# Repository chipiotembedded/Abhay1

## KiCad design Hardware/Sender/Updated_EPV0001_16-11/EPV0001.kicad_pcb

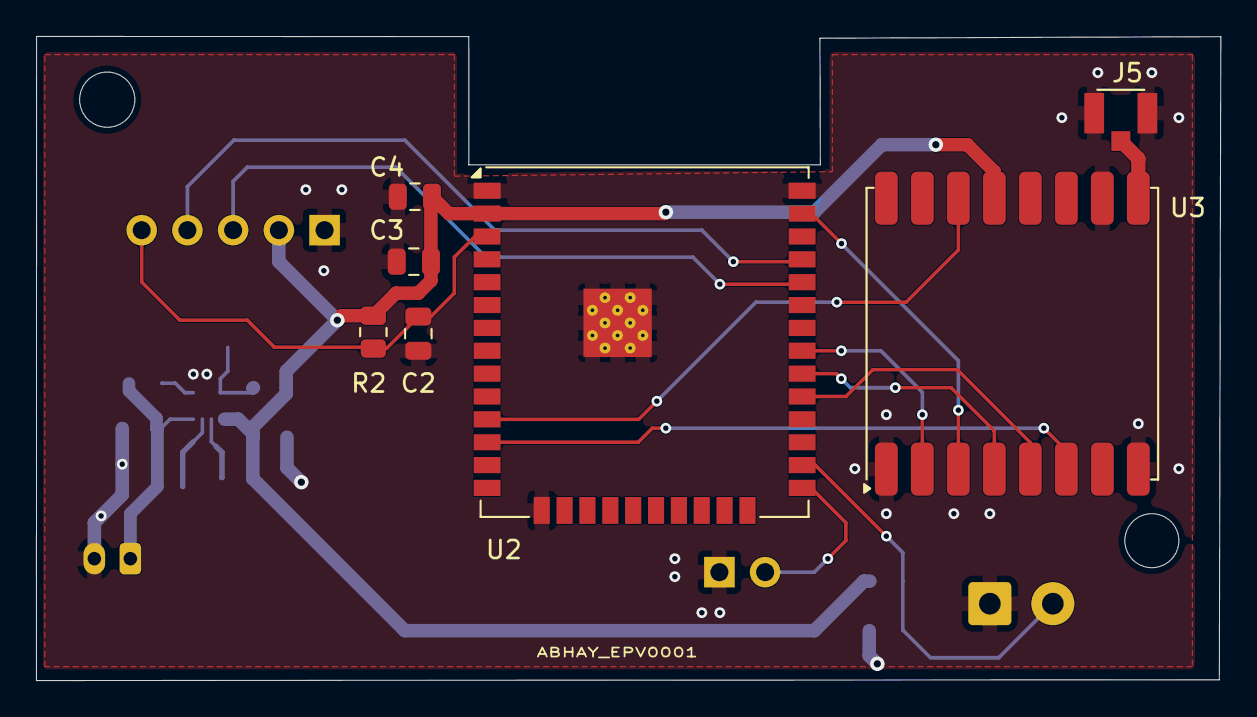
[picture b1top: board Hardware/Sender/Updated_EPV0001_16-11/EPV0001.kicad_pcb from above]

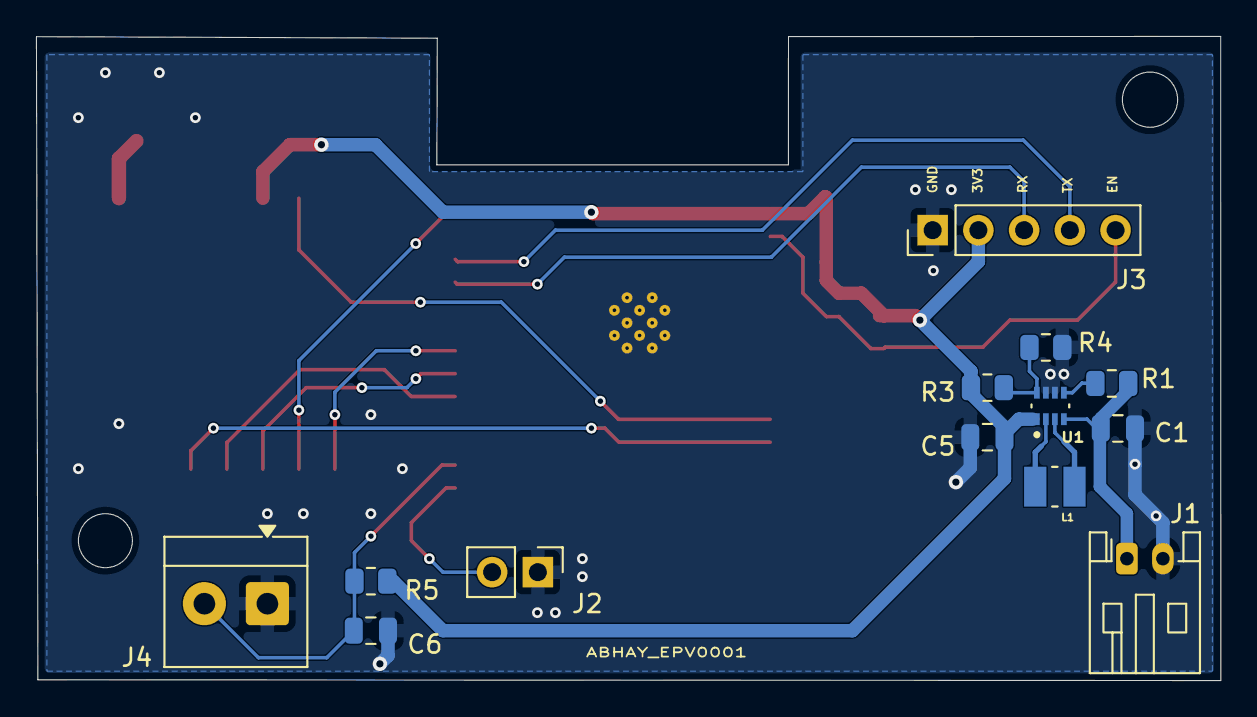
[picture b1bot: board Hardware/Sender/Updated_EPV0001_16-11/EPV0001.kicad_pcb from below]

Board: 2 copper layers, 65.8 x 35.8 mm, 20 parts (13 on the bottom side), 19 nets.

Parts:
C1, C3: 22uf; C_0805_2012Metric
C2, C4, C6: 0.1uf; C_0805_2012Metric
C5: 47 uF; C_0805_2012Metric
J1: batt IN; JST_PH_S2B-PH-K_1x02_P2.00mm_Horizontal
J2: Boot Button; PinHeader_1x02_P2.54mm_Vertical
J3: Code_Flasher; PinHeader_1x05_P2.54mm_Vertical
J4: Main switch; TerminalBlock_4Ucon_1x02_P3.50mm_Horizontal
J5: U.FL-R-SMT_01_; HRS_U.FL-R-SMT_01_
L1: DFE252012P-1R0M=P2; INDC2520X120N
R1: 100k ohm; R_0805_2012Metric
R2, R5: 10k; R_0805_2012Metric
R3: 511k ohm; R_0805_2012Metric
R4: 91k ohm; R_0805_2012Metric
U1: TPS631000DRLR; SOT50P160X60-8N
U2: ESP32-WROOM-32UE
U3: RFM95W-868S2; HOPERF_RFM9XW_SMD

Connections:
+3.3V: C3.1, C4.1, C5.1, J3.2, R2.1, R3.1, R5.1, U1.1 (VOUT), U2.2 (VDD), U3.13 (3.3V)
GND: C1.2, C2.1, C3.2, C4.2, C5.2, C6.1, J1.2, J2.1, J3.1, J4.1, J5.1 (GND), J5.2 (GND), R4.2, U1.6 (MODE), U1.7 (GND), U2.1 (GND), U2.15 (GND), U2.38 (GND), U2.39 (GND), U3.1 (GND), U3.8 (GND), U3.10 (GND)
unnamed: C1.1, J1.1, R1.1, U1.4 (VIN)
unnamed: J2.2, U2.25 (IO0)
unnamed: J3.3, U2.34 (RXD0/IO3)
unnamed: J3.4, U2.35 (TXD0/IO1)
unnamed: C2.2, J3.5, R2.2, U2.3 (EN)
unnamed: C6.2, J4.2, R5.2, U2.26 (IO4)
unnamed: J5.3 (SIG), U3.9 (ANT)
unnamed: R1.2, U1.5 (EN)
unnamed: R3.2, R4.1, U1.8 (FB)
unnamed: L1.1, U1.3 (LX1)
unnamed: L1.2, U1.2 (LX2)
unnamed: U2.29 (IO5), U3.5 (NSS)
unnamed: U2.30 (IO18), U3.4 (SCK)
unnamed: U2.31 (IO19), U3.2 (MISO)
unnamed: U2.37 (IO23), U3.3 (MOSI)
unnamed: U2.11 (IO26), U3.14 (DIO0)
unnamed: U2.12 (IO27), U3.6 (RESET)

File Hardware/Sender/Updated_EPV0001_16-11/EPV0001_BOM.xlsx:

Reference | Value | Footprint/ Discription | Datasheet | Qty | MANUFACTURER
C1,C3 | 22uf | Capacitor_SMD:C_0805_2012Metric | GRM187R61A226ME15, 22 µF, 6.3 V | 2 | Murata
C2,C4,C6 | 0.1uf | Capacitor_SMD:C_0805_2012Metric |  | 3
C5 | 47 uF | Capacitor_SMD:C_0805_2012Metric | GRM219R60J476ME44, 47 µF, 6.3 V | 1 | Murata
J1 | batt IN | Connector_JST:JST_PH_S2B-PH-K_1x02_P2.00mm_Horizontal |  | 1
J2 | Boot Button | Connector_PinHeader_2.54mm:PinHeader_1x02_P2.54mm_Vertical |  | 1
J3 | Code_Flasher | Connector_PinHeader_2.54mm:PinHeader_1x05_P2.54mm_Vertical |  | 1
J4 | Main switch | TerminalBlock_4Ucon:TerminalBlock_4Ucon_1x02_P3.50mm_Horizontal |  | 1
J5 | U.FL-R-SMT_01_ | LORA Antenna:HRS_U.FL-R-SMT_01_ |  | 1
L1 | 1 uH | Inductor_SMD:L_APV_ANR252012 | DFE252012P-1R0M=P2 | 1 | Murata
R1 | 100k ohm | Resistor_SMD:R_0805_2012Metric |  | 1
R2,R5 | 10k | Resistor_SMD:R_0805_2012Metric |  | 2
R3 | 511k ohm | Resistor_SMD:R_0805_2012Metric |  | 1
R4 | 91k ohm | Resistor_SMD:R_0805_2012Metric |  | 1
U1 | TPS631000DRLR | TPS631000DRLR:SOT50P160X60-8N | https://www.ti.com/product/TPS631000/part-details/TPS631000DRLR | 1 | Texas Instruments
U2 | ESP32-WROOM-32UE | RF_Module:ESP32-WROOM-32UE | https://www.espressif.com/sites/default/files/documentation/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 | 1
U3 | RFM95W-868S2 | RF_Module:HOPERF_RFM9XW_SMD | https://www.hoperf.com/data/upload/portal/20181127/5bfcbea20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 | 1
 | TP4056 | TP4056 1A Li Ion Lithium Battery Charging Module With Current Protection Type C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 | https://robu.in/product/tp4056-1a-li-ion-lithium-battery-cha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 | 1
 | TP4056 Panel Mount 3D Printed Housing | TP4056 USB-C Panel Mount 3D Printed Housing enclosure that securely houses the 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 | https://www.amazon.in/Printed-Snap-Fit-Enclosure-Electronics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 | 1
 | Lipo battery | 3.7V 2000mAh Li-Po Rechargeable Battery (Lithium Polymer Battery Pack) | https://rajivelectronics.com/product/3-7v-2000mah-li-po-rech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 | 1
 | Interface cable | SMA FEMALE TO UFL ANTENNA EXT -200MM | https://rajivelectronics.com/product/sma-female-to-ufl-anten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 | 1
 | ANTENNA | 2.4 GHZ/3 DB AT 5 GHZ SMA MALE RUBBER DUCK WIFI FOLDING ANTENNA-105 MM | https://rajivelectronics.com/product/2-4ghz-5ghz-sma-male-ru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
 | JST - Connector with wire | JST-PH-2 -2 Pin Double Sided Female To Female Connector With 2mm Pitch -30cm Wi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 | https://sharvielectronics.com/product/jst-ph-2-2-pin-double-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 | 1
 | Main button | Door Exit Metel push buttorn |  | 1
 | Enclosure metel box with screw

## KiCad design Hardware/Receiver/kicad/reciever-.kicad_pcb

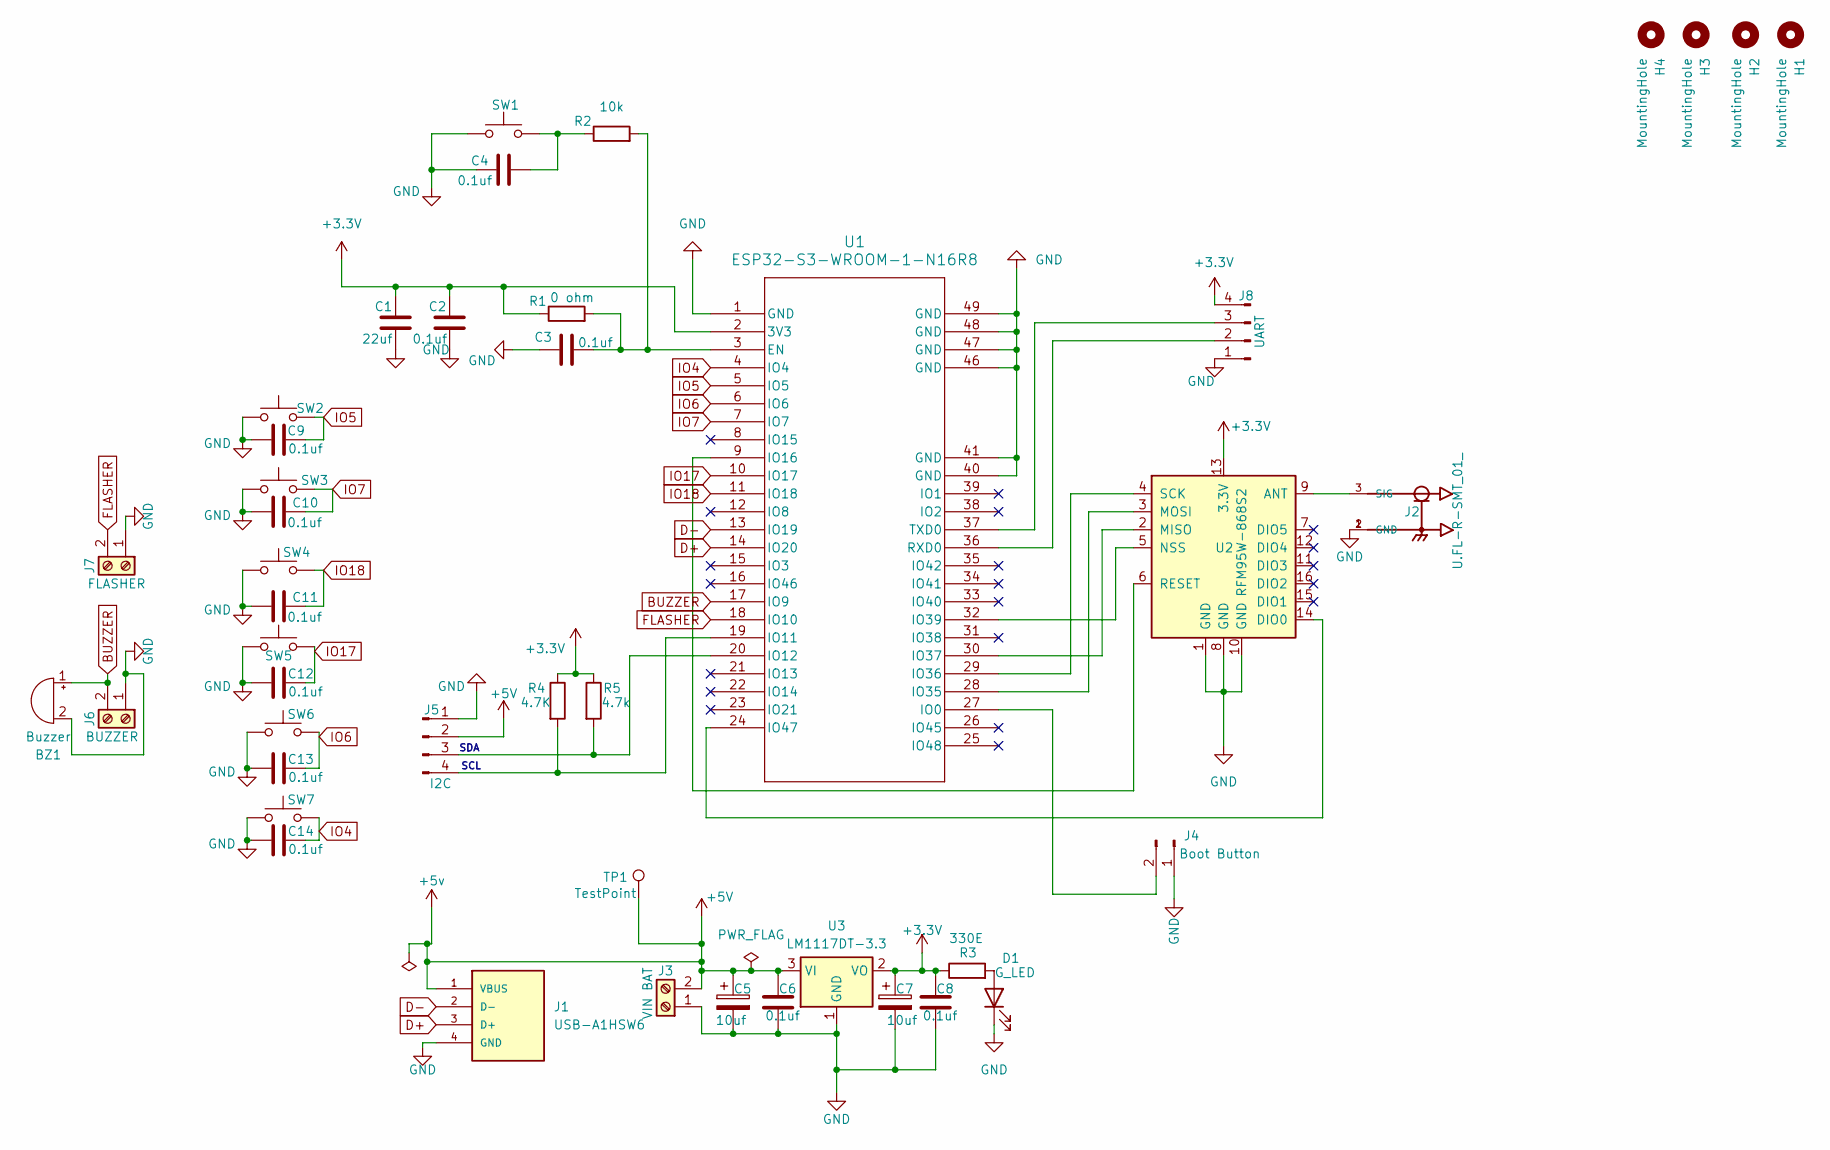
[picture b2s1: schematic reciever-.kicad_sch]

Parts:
BZ1: Buzzer; Buzzer_TDK_PS1240P02BT_D12.2mm_H6.5mm
C1: 22uf; C_0805_2012Metric_Pad1.18x1.45mm_HandSolder
C2, C3, C4, C6, C8, C9, C10, C11, C12, C13, C14: 0.1uf; C_0603_1608Metric_Pad1.08x0.95mm_HandSolder
C5, C7: 10uf; C_0805_2012Metric_Pad1.18x1.45mm_HandSolder
D1: G_LED; LED_0805_2012Metric_Pad1.15x1.40mm_HandSolder
H1, H2, H3, H4: MountingHole; MountingHole_3.5mm_Pad
J1: USB-A1HSW6; USB_A_Molex_67643_Horizontal
J2: U.FL-R-SMT_01_; HRS_U.FL-R-SMT_01_
J3: VIN BAT; TerminalBlock_bornier-2_P5.08mm
J4: Boot Button; PinHeader_1x02_P2.54mm_Vertical
J5: I2C; PinHeader_1x04_P2.54mm_Vertical
J6: BUZZER; TerminalBlock_bornier-2_P5.08mm
J7: FLASHER; TerminalBlock_bornier-2_P5.08mm
J8: UART; PinSocket_1x04_P2.54mm_Vertical
R1: 0 ohm; R_0805_2012Metric_Pad1.20x1.40mm_HandSolder
R2: 10k; R_0805_2012Metric_Pad1.20x1.40mm_HandSolder
R3: 330E; R_0805_2012Metric_Pad1.20x1.40mm_HandSolder
R4: 4.7K; R_0805_2012Metric
R5: 4.7k; R_0805_2012Metric
SW1: SW_Push; SW_PUSH_6mm_H7.3mm
SW2: NUM_2; SW_PUSH-12mm
SW3: UP; SW_PUSH-12mm
SW4: SILENCE; SW_PUSH-12mm
SW5: NEXT; SW_PUSH-12mm
SW6: Back/Cancle; SW_PUSH-12mm
SW7: NUM_1; SW_PUSH-12mm
TP1: TestPoint; TestPoint_Pad_D1.5mm
U1: ESP32-S3-WROOM-1-N16R8; ESP32-S3-WROOM-1_EXP
U2: RFM95W-868S2; Ai-Thinker-Ra-01-LoRa
U3: LM1117DT-3.3; TO-252-3_TabPin2

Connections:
+3.3V: C1.1, C2.1, C7.1, C8.1, J8.4, R1.1, R3.1, R4.1, R5.1, U1.2 (3V3), U2.13 (3.3V), U3.2 (VO)
+5V: C5.1, C6.1, J1.1 (VBUS), J3.2, J5.2, TP1.1, U3.3 (VI)
BUZZER: BZ1.1 (+), J6.2, U1.17 (IO9)
D+: J1.3 (D+), U1.14 (IO20)
D-: J1.2 (D-), U1.13 (IO19)
FLASHER: J7.2, U1.18 (IO10)
GND: BZ1.2 (-), C1.2, C2.2, C3.1, C4.1, C5.2, C6.2, C7.2, C8.2, C9.1, C10.1, C11.1, C12.1, C13.1, C14.1, D1.1 (K), J1.4 (GND), J2.1 (GND), J2.2 (GND), J3.1, J4.1, J5.1, J6.1, J7.1, J8.1, SW1.1, SW2.1, SW3.1, SW4.1, SW5.1, SW6.1, SW7.1, U1.1 (GND), U1.40 (GND), U1.41 (GND), U1.42, U1.43, U1.44, U1.45, U1.46 (GND), U1.47 (GND), U1.48 (GND), U1.49 (GND), U2.1 (GND), U2.8 (GND), U2.10 (GND), U3.1 (GND); also elsewhere on the board
IO4: C14.2, SW7.2, U1.4 (IO4)
IO5: C9.2, SW2.2, U1.5 (IO5)
IO6: C13.2, SW6.2, U1.6 (IO6)
IO7: C10.2, SW3.2, U1.7 (IO7)
IO17: C12.2, SW5.2, U1.10 (IO17)
IO18: C11.2, SW4.2, U1.11 (IO18)
unnamed: C4.2, R2.1, SW1.2
unnamed: D1.2 (A), R3.2
unnamed: J2.3 (SIG), U2.9 (ANT)
unnamed: J4.2, U1.27 (IO0)
unnamed: J5.3, R5.2, U1.20 (IO12)
unnamed: J5.4, R4.2, U1.19 (IO11)
unnamed: J8.2, U1.36 (RXD0)
unnamed: J8.3, U1.37 (TXD0)
unnamed: C3.2, R1.2, R2.2, U1.3 (EN)
unnamed: U1.9 (IO16), U2.6 (RESET)
unnamed: U1.28 (IO35), U2.3 (MOSI)
unnamed: U1.29 (IO36), U2.4 (SCK)
unnamed: U1.30 (IO37), U2.2 (MISO)
unnamed: U1.32 (IO39), U2.5 (NSS)
unnamed: U1.24 (IO47), U2.14 (DIO0)

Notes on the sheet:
SDA
SCL

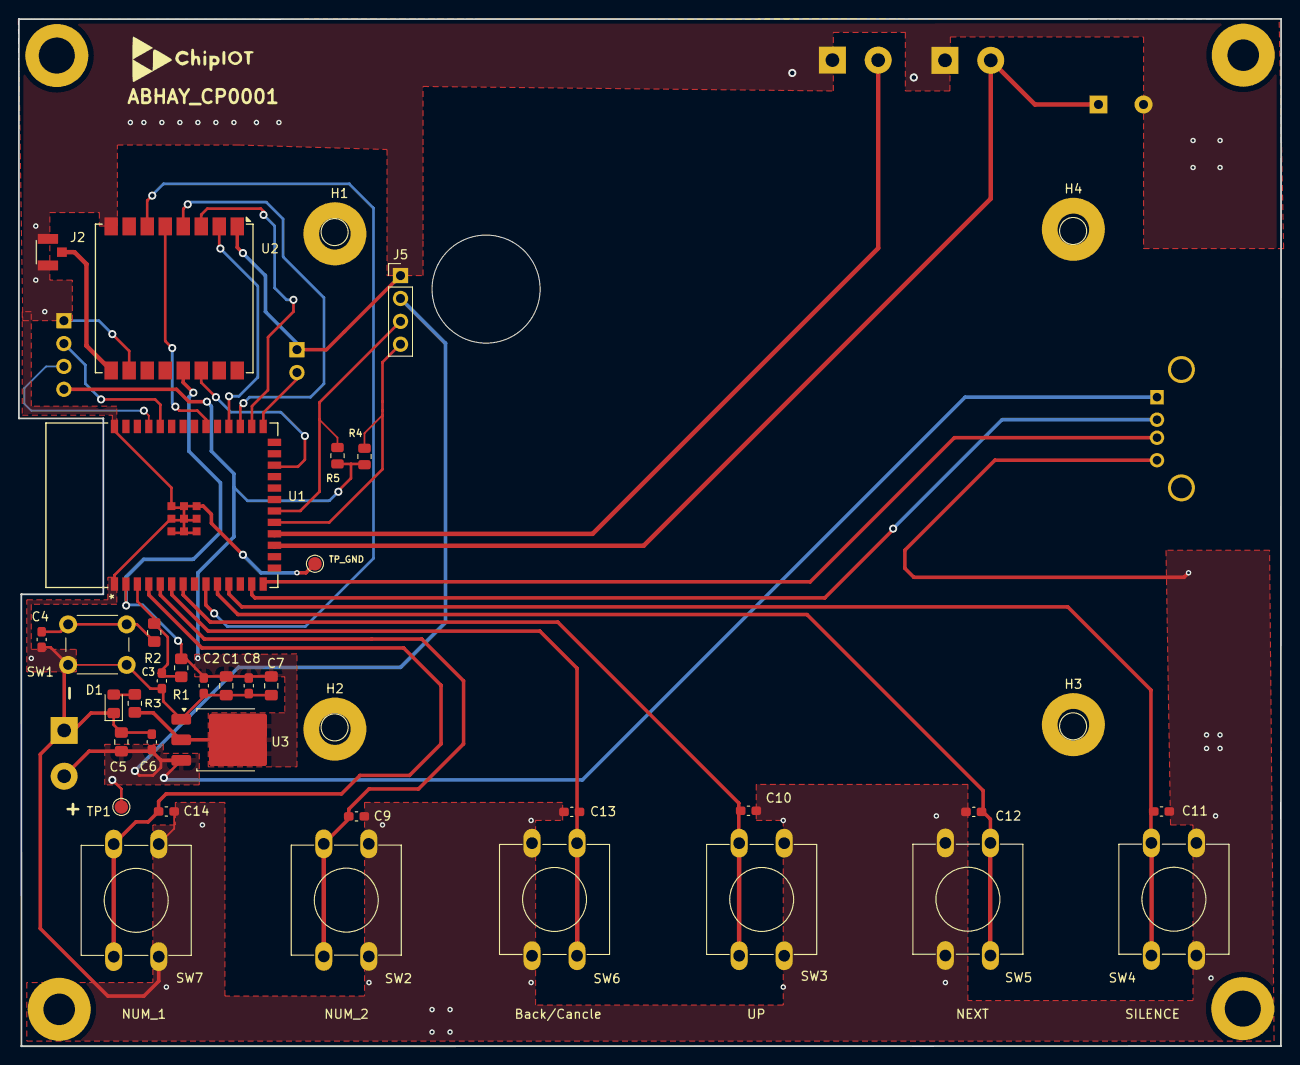
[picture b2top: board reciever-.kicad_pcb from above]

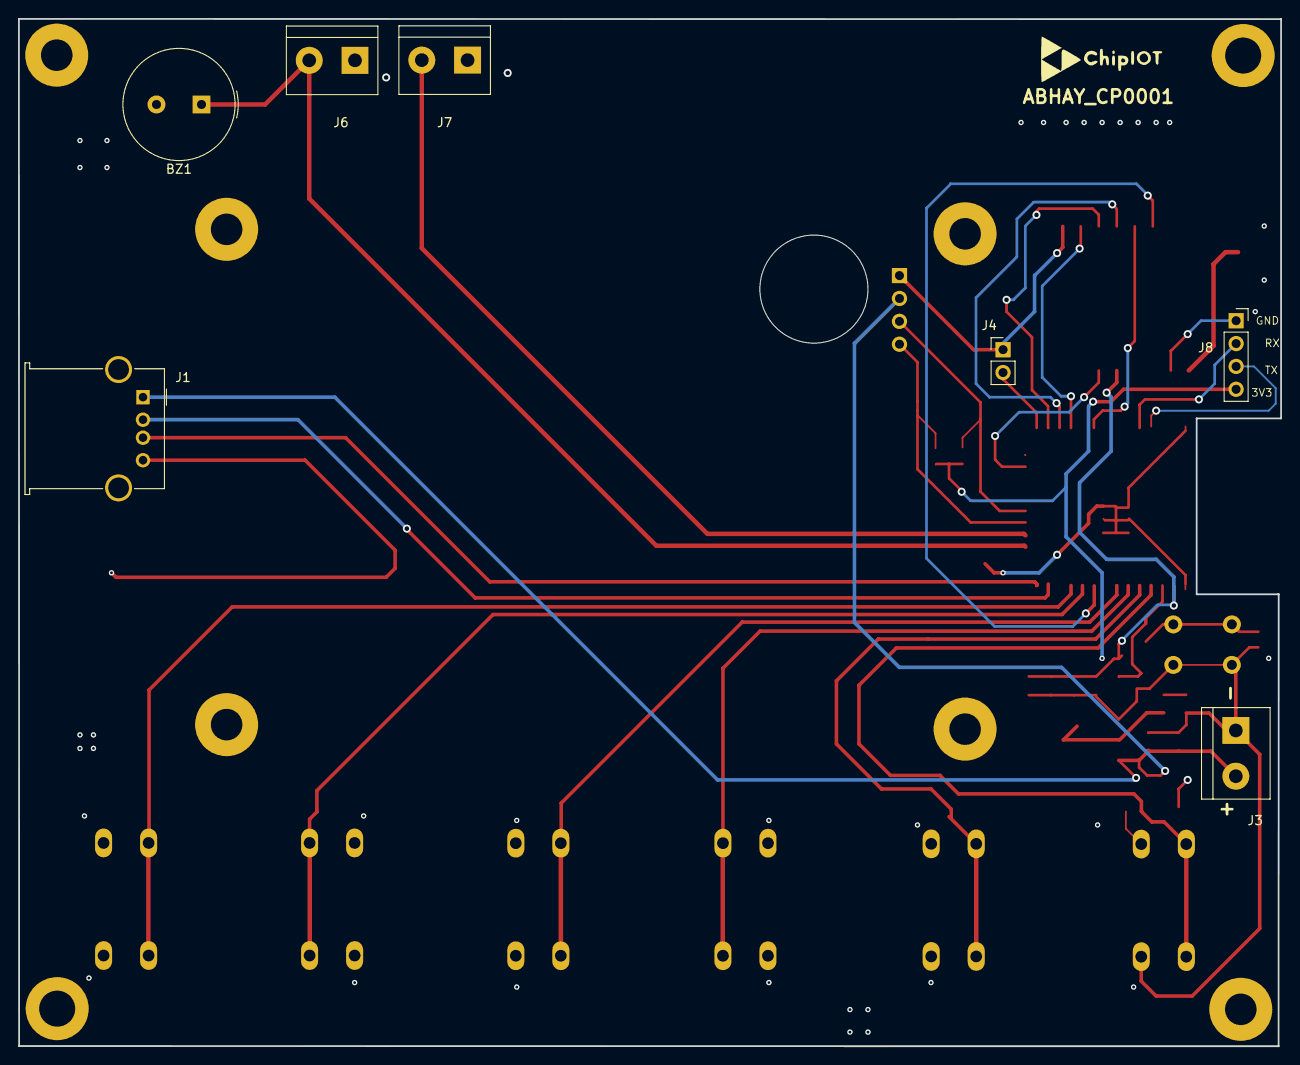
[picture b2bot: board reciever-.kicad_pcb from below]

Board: 2 copper layers, 140.2 x 114.1 mm, 45 parts (7 on the bottom side), 28 nets.

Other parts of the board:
TP_GND: TestPoint_Pad_D1.5mm

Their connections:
GND: TP_GND.1; also elsewhere on the board

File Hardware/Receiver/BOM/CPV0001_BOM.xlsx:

CPV0001 - BOM
Reference | Value | Footprint | QTY | Price (1 pc) IN RS
C1 | 22uF | Capacitor_SMD:C_0805_2012Metric_Pad1.18x1.45mm_HandSolder | 1 | 1
C2, C3, C4, C6, C8, C9, C10, C11, C12, C13,C14 | 0.1uF | Capacitor_SMD:C_0603_1608Metric_Pad1.08x0.95mm_HandSolder | 11 | 0.35
C5, C7 | 10uF | Capacitor_SMD:C_0805_2012Metric_Pad1.18x1.45mm_HandSolder | 2 | 1.5
D1 | G_LED | LED_SMD:LED_0805_2012Metric_Pad1.15x1.40mm_HandSolder | 1 | 1
J1 | USB Type A Right Angle Female Connector | Connector_USB:USB_A_Molex_67643_Horizontal | 1 | 5
J2 | UFL MALE CONNECTOR SMD | ufl:HRS_U.FL-R-SMT_01_ | 1 | 10
 | 2.4 GHZ/3 DB AT 5 GHZ SMA MALE RUBBER DUCK WIFI FOLDING ANTENNA-105 MM |  | 1 | 55
 | SMA FEMALE TO UFL ANTENNA EXT -200MM |  | 1 | 35
J3 | VIN BAT (screw terminal ) | TerminalBlock:TerminalBlock_bornier-2_P5.08mm | 1 | 3
J4 | Boot Button (burgstrips ) | Connector_PinHeader_2.54mm:PinHeader_1x02_P2.54mm_Vertical | 1 | 5
J5 | I2C (Pin 2.54 mm Pitch Male Berg Strip Straight Single Row Header 15 mm Height 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 | Connector_PinHeader_2.54mm:PinHeader_1x04_P2.54mm_Vertical | 1 | 10
J6 | BUZZER (screw terminal ) | TerminalBlock:TerminalBlock_bornier-2_P5.08mm | 1 | 3
J7 | FLASHER (screw terminal ) | TerminalBlock:TerminalBlock_bornier-2_P5.08mm | 1 | 3
J8 | UART (Code_Flasher (burgstrips )) | Connector_PinSocket_2.54mm:PinSocket_1x04_P2.54mm_Vertical | 1 | 5
R1 | 0 ohm (Resistor) | Resistor_SMD:R_0805_2012Metric_Pad1.20x1.40mm_HandSolder | 1 | 0.5
R2 | 10k (Resistor) | Resistor_SMD:R_0805_2012Metric_Pad1.20x1.40mm_HandSolder | 1 | 0.5
R3 | 330E (Resistor) | Resistor_SMD:R_0805_2012Metric_Pad1.20x1.40mm_HandSolder | 1 | 0.5
SW1 | SW_Push | Button_Switch_THT:SW_PUSH_6mm_H7.3mm | 1 | 3
SW2.SW3,SW4,SW5,SW6,SW7 | NUM_1,NUM_2,UP,BACK,NEXT,SILANCE | Button_Switch_THT:SW_PUSH-12mm , 12 x 12 x 20 mm Momentary Tactile Switch 4 Pin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 | 6 | 10
U1 | ESP32-S3-WROOM-1-N16R8 | esp3 s3:ESP32-S3-WROOM-1_EXP | 1 | 356
U2 | RFM95W-868S2 (lora module ) | RF_Module:Ai-Thinker-Ra-01-LoRa | 1 | 500
U3 | LM1117DT-3.3 (regulator ) | Package_TO_SOT_SMD:TO-252-3_TabPin2 | 1 | 5
Adapter | 5 v |  | 1 | 150
METAL SPACERS THREADED MS-10 | 10MM |  |  | 5
POWER Jack | 2.1x5.5mm DC Power Jack Socket Panel Mount (Female) - |  | 1 | 10
cable gland | Polyamide Cable Gland PG 9 |  | 1 | 20
Enclosure metel box with screw |  |  | 1 | 500
16X 4 LCD | 16X4 GREEN LCD JHD Make |  | 1 | 315
 |  | Manufacturing cost (PCB) |  | 1200
 |  | Total |  | 3213.35

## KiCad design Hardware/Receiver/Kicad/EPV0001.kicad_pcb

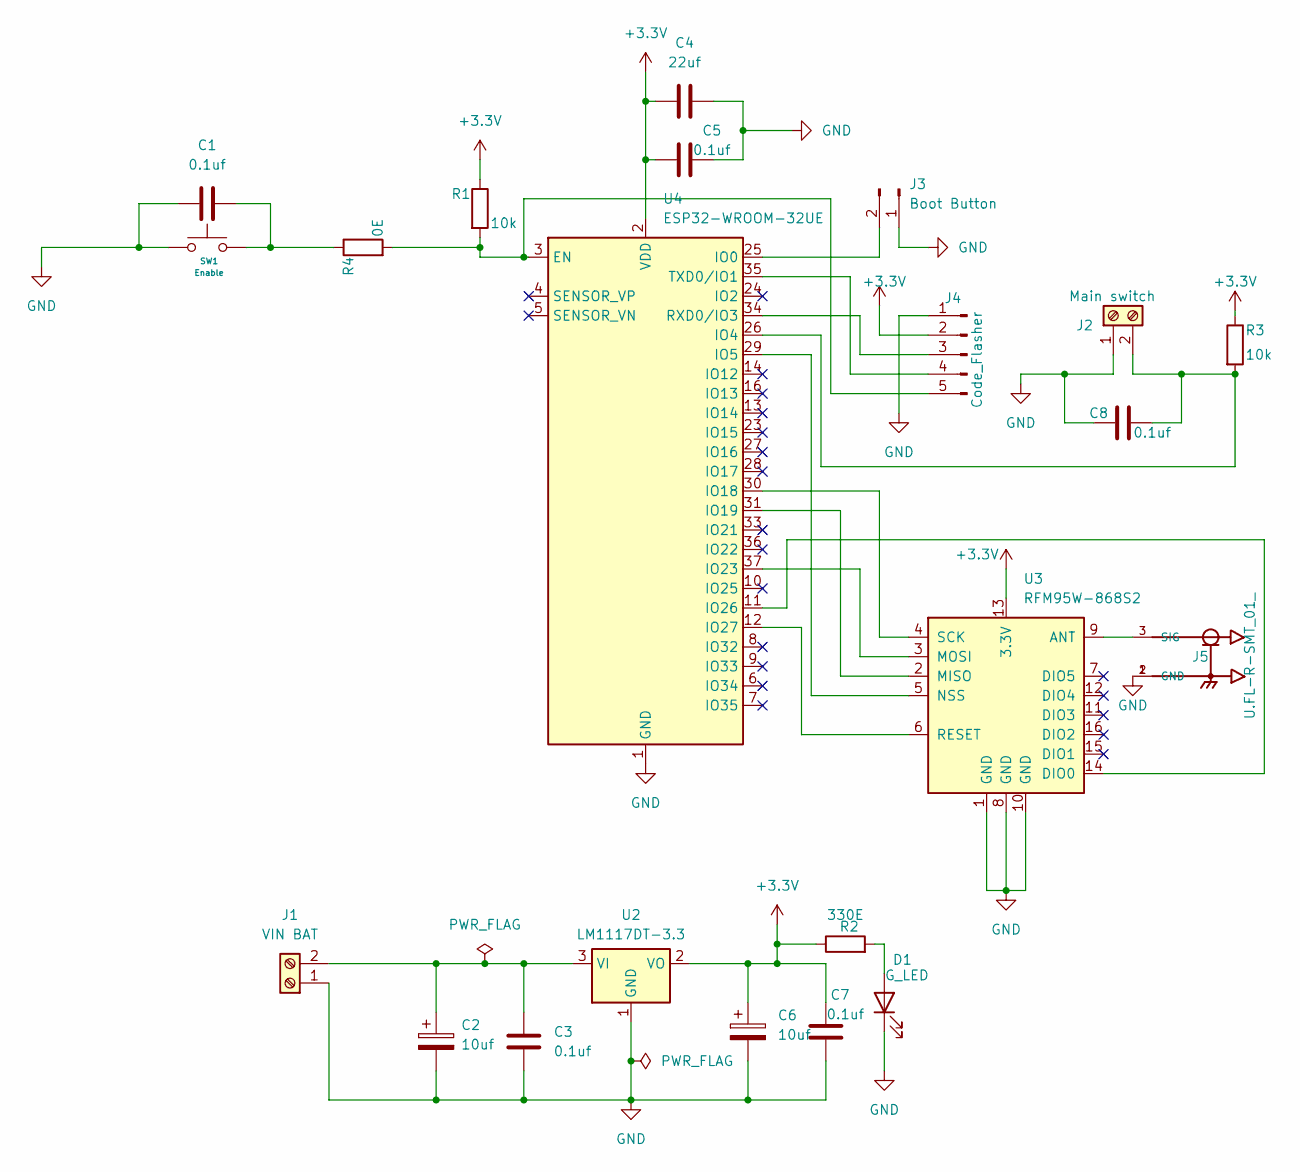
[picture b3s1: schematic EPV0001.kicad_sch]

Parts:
C1, C3, C5, C7, C8: 0.1uf; C_0805_2012Metric
C2, C6: 10uf; C_0805_2012Metric
C4: 22uf; C_0805_2012Metric
D1: G_LED; LED_0805_2012Metric_Pad1.15x1.40mm_HandSolder
J1: VIN BAT; TerminalBlock_bornier-2_P5.08mm
J2: Main switch; TerminalBlock_bornier-2_P5.08mm
J3: Boot Button; PinHeader_1x02_P2.54mm_Vertical
J4: Code_Flasher; PinHeader_1x05_P2.54mm_Vertical
J5: U.FL-R-SMT_01_; u3
R1, R3: 10k; R_0805_2012Metric
R2: 330E; R_0805_2012Metric_Pad1.20x1.40mm_HandSolder
R4: 0E; R_0805_2012Metric
SW1: Enable; SW4_1825910-D_TEC
U2: LM1117DT-3.3; TO-252-3_TabPin2
U3: RFM95W-868S2; HOPERF_RFM9XW_SMD
U4: ESP32-WROOM-32UE

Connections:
+3.3V: C4.1, C5.1, C6.1, C7.1, J4.2, R1.1, R2.1, R3.1, U2.2 (VO), U3.13 (3.3V), U4.2 (VDD)
GND: C1.1, C2.2, C3.2, C4.2, C5.2, C6.2, C7.2, C8.1, D1.1 (K), J1.1, J2.1, J3.1, J4.1, J5.1 (GND), J5.2 (GND), SW1.1, U2.1 (GND), U3.1 (GND), U3.8 (GND), U3.10 (GND), U4.1 (GND), U4.15 (GND), U4.38 (GND), U4.39 (GND)
unnamed: C1.2, R4.1, SW1.2
unnamed: D1.2 (A), R2.2
unnamed: C2.1, C3.1, J1.2, U2.3 (VI)
unnamed: C8.2, J2.2, R3.2, U4.26 (IO4)
unnamed: J3.2, U4.25 (IO0)
unnamed: J4.3, U4.34 (RXD0/IO3)
unnamed: J4.4, U4.35 (TXD0/IO1)
unnamed: J4.5, R1.2, R4.2, U4.3 (EN)
unnamed: J5.3 (SIG), U3.9 (ANT)
unnamed: U3.14 (DIO0), U4.11 (IO26)
unnamed: U3.2 (MISO), U4.31 (IO19)
unnamed: U3.3 (MOSI), U4.37 (IO23)
unnamed: U3.5 (NSS), U4.29 (IO5)
unnamed: U3.6 (RESET), U4.12 (IO27)
unnamed: U3.4 (SCK), U4.30 (IO18)

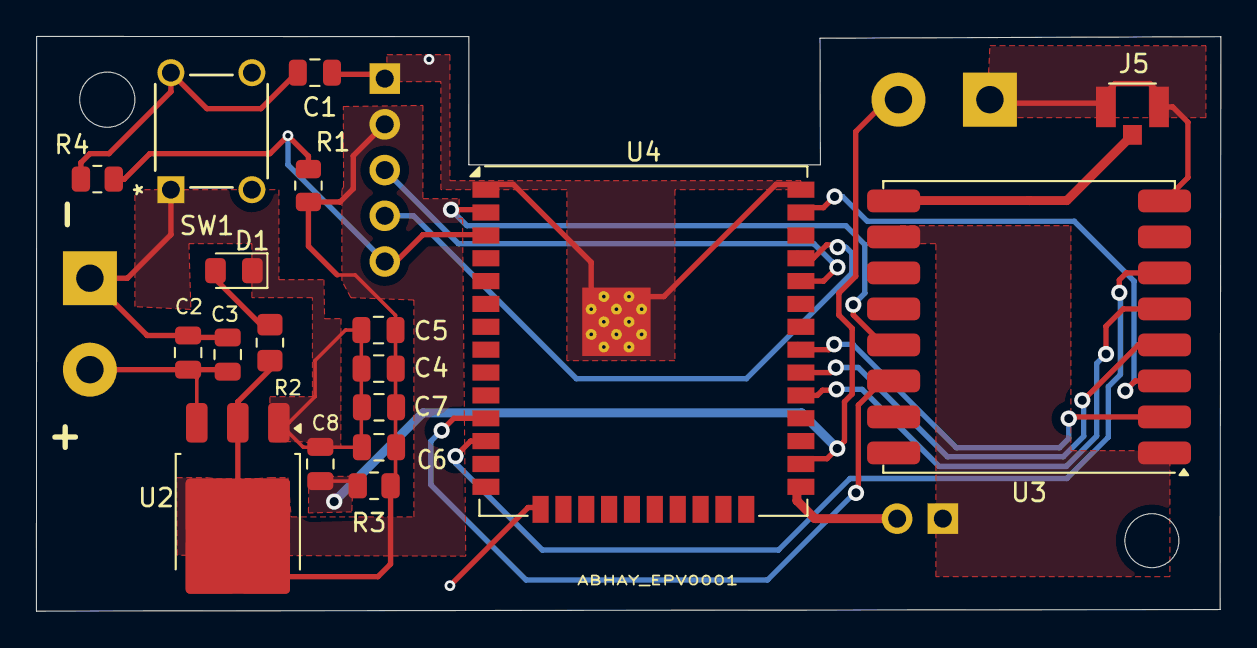
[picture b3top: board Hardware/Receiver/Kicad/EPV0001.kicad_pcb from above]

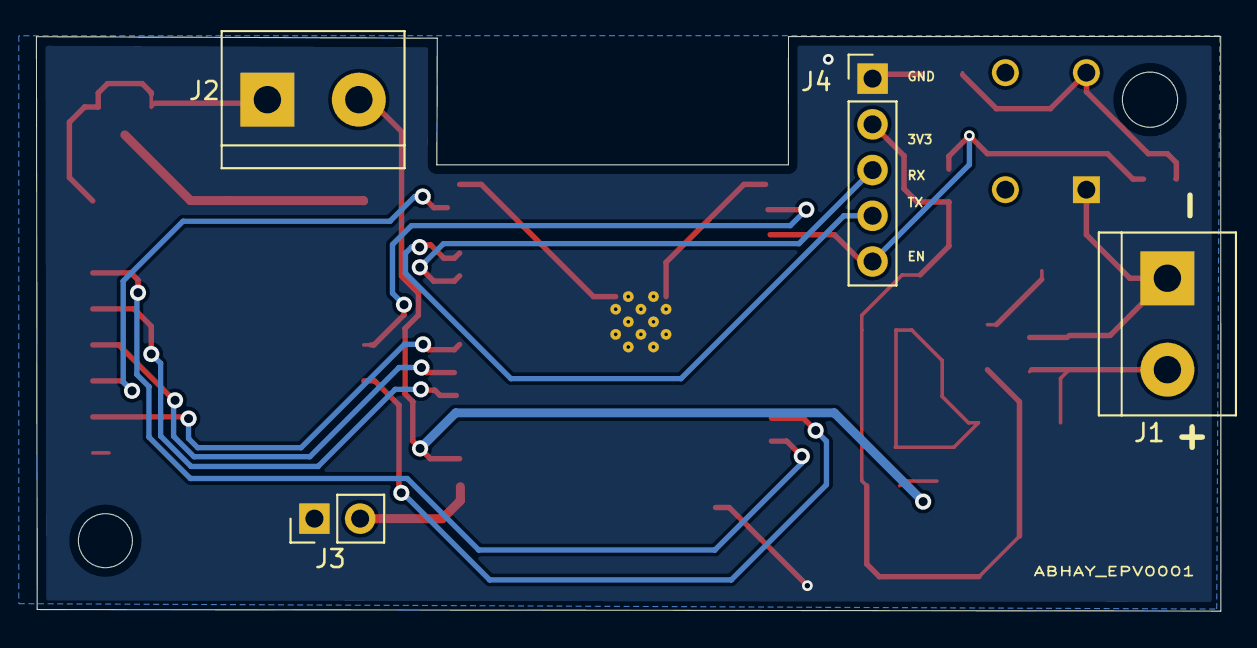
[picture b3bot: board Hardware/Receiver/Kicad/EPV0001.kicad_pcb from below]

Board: 2 copper layers, 65.8 x 31.9 mm, 22 parts (4 on the bottom side), 17 nets.
